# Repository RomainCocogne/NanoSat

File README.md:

### Desciption
This repo is the current work of the Smart Solar Panel Project, an auxiliary project of NiceCube.
NiceCube is a NanoSatellite project.

You can find further informations on this project following 

### Clone
If you want to clone this repo and continue the project, you need to be aware of some points

  - The code can be used as it is, but you should be carefull if you use another microcontroller. There may be some registers that need to be changed
  
  - The kicad projects use library included into this repo. If you open them as it is you might need to change the access path in kicad parameter tho.

### Contact
You can contact us using the following email adress

camille.brunin@univ-cotedazur.fr

quentin.combal@univ-cotedazur.fr

romain.cocogne@univ-cotedazur.fr

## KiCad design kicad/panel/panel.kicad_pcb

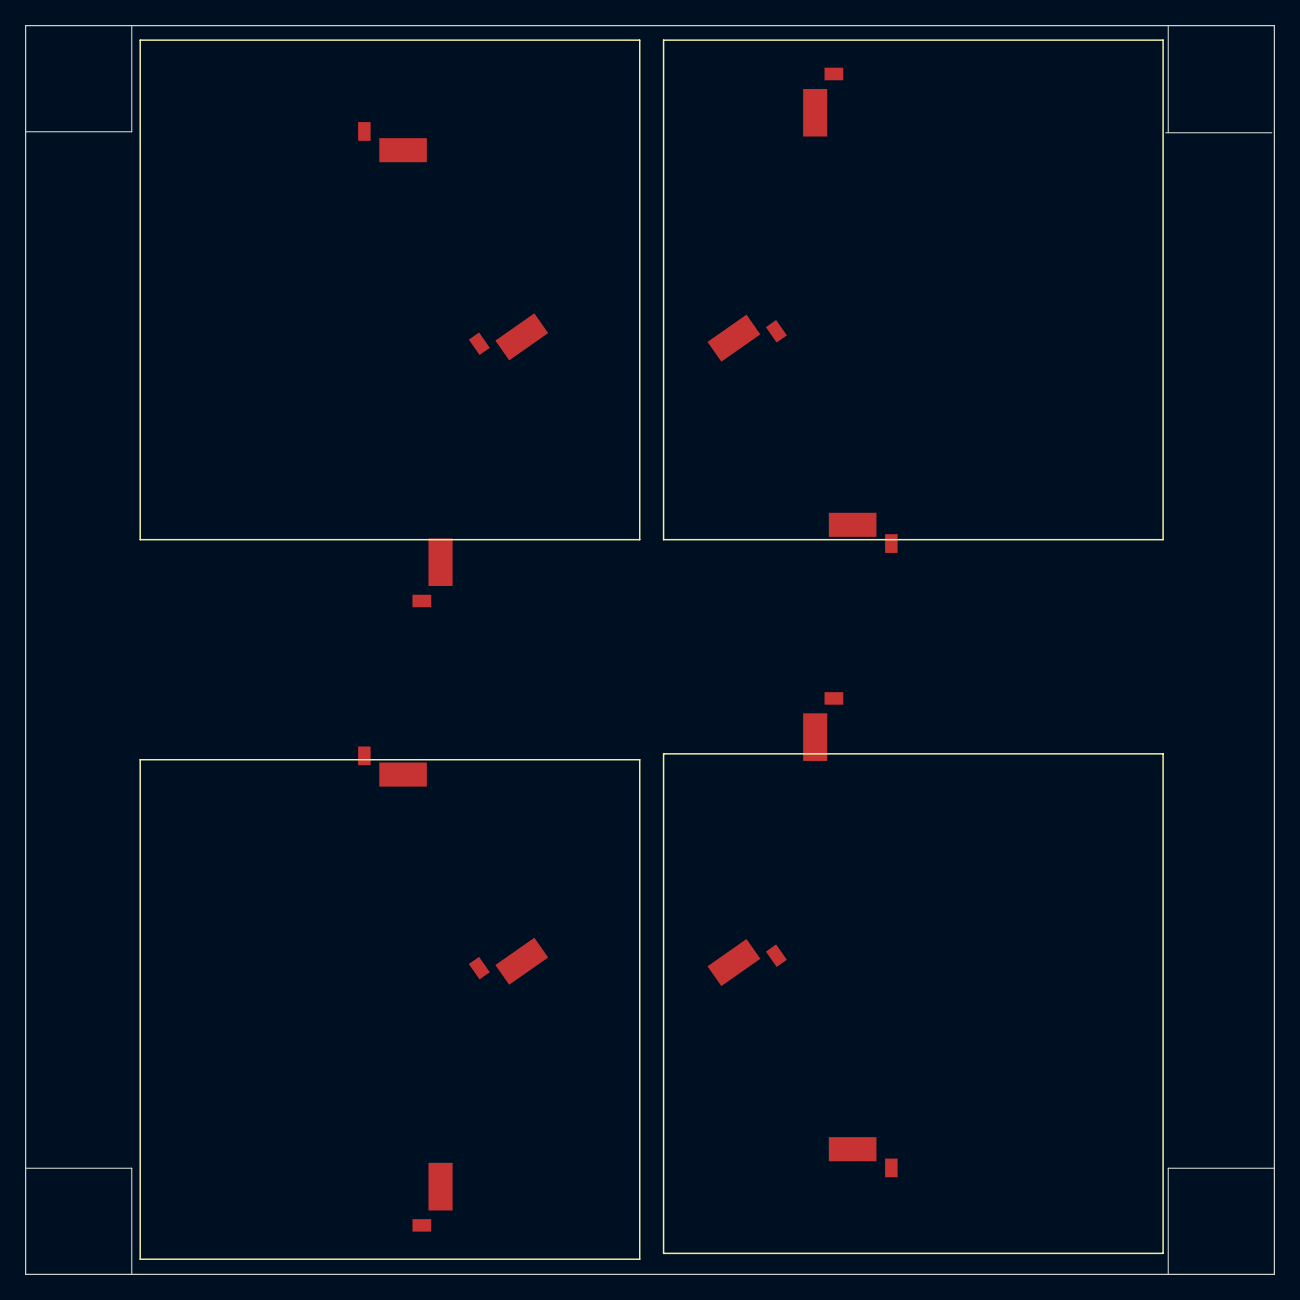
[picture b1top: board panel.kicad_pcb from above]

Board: 2 copper layers, 100.0 x 100.0 mm, 12 parts (0 on the bottom side), 11 nets, no tracks yet.

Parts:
SC1, SC2, SC3, SC4, SC5, SC6, SC7, SC8, SC9, SC10, SC11, SC12: Solar_Cell; TRISOLX-T01

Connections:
GND: SC4.2, SC8.2, SC12.2
unnamed: SC1.2, SC2.1
unnamed: SC2.2, SC3.1
unnamed: SC3.2, SC4.1
unnamed: SC5.2, SC6.1
unnamed: SC6.2, SC7.1
unnamed: SC7.2, SC8.1
unnamed: SC9.2, SC10.1
unnamed: SC10.2, SC11.1
unnamed: SC11.2, SC12.1
VCC: SC1.1, SC5.1, SC9.1

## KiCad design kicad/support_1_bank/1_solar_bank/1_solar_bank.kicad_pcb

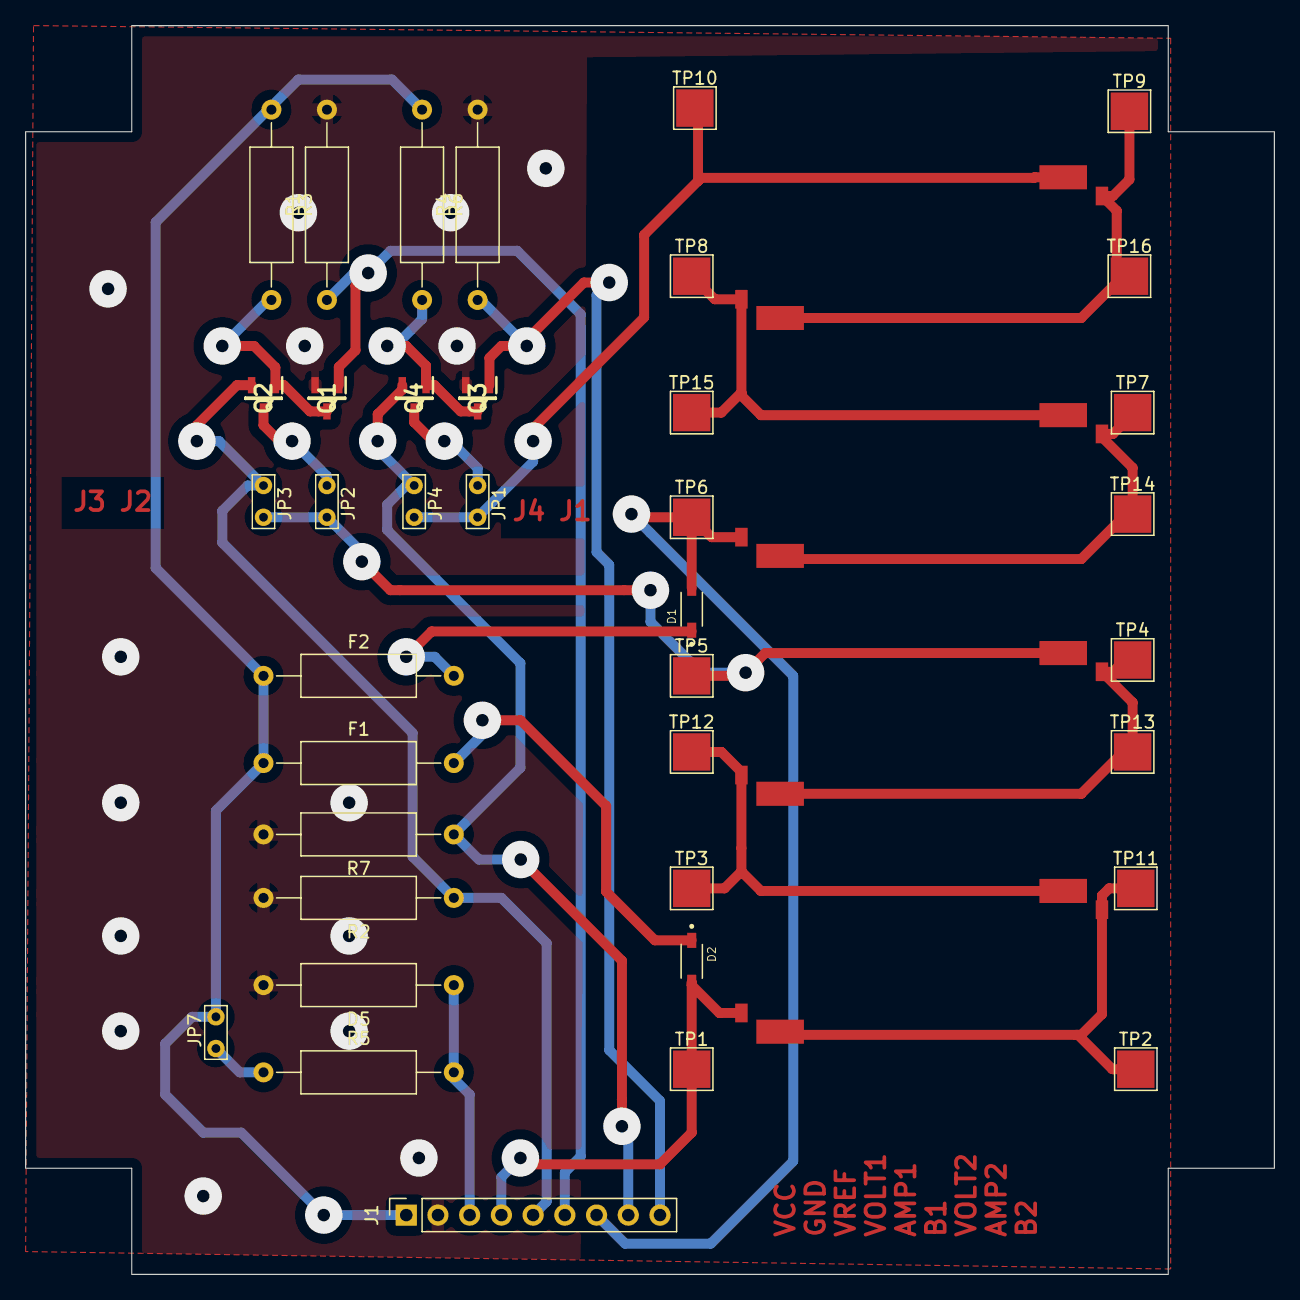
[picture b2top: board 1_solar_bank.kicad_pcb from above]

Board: 2 copper layers, 100.0 x 100.0 mm, 46 parts (0 on the bottom side), 24 nets.

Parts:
D1, D2: D_Schottky; SOD3715X135N
D5: D_Zener; R_Axial_DIN0309_L9.0mm_D3.2mm_P15.24mm_Horizontal
F1, F2: Fuse_Small; R_Axial_DIN0309_L9.0mm_D3.2mm_P15.24mm_Horizontal
J1: Conn_01x09; PinSocket_1x09_P2.54mm_Vertical
JP1, JP2, JP3, JP4, JP7: Jumper_2_Bridged; TestPoint_Bridge_Pitch2.54mm_Drill0.7mm
Q1, Q2, Q3, Q4: RUR040N02HZGTL
R1, R2, R4, R7: 20R; R_Axial_DIN0309_L9.0mm_D3.2mm_P15.24mm_Horizontal
R3, R5, R6: 1M; R_Axial_DIN0309_L9.0mm_D3.2mm_P15.24mm_Horizontal
SC1, SC2, SC3, SC4, SC5, SC6, SC7, SC8: Solar_Cell; TRISOLX-T01
TP1, TP2, TP3, TP4, TP5, TP6, TP7, TP8, TP9, TP10, TP11, TP12, TP13, TP14, TP15, TP16: TestPoint; TestPoint_Pad_3.0x3.0mm

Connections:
+VSW: F1.1, F2.1, J1.1, JP7.1, R3.1, R6.1
AMPERMETER1: J1.5, JP3.2, Q2.3, R2.1
AMPERMETER2: J1.8, JP4.2, Q4.3, R7.1
BNK1_CONTROL: J1.6, Q1.1, R1.1
BNK2_CONTROL: J1.9, Q3.1, R4.1
GND: D5.2, J1.2, Q1.3, Q3.3, R1.2, R2.2, R4.2, R7.2
unnamed: D1.1, F2.2
unnamed: D2.1, F1.2
unnamed: JP1.1, JP4.1, SC8.2, TP10.1
unnamed: JP1.2, Q4.2
unnamed: JP2.1, JP3.1, SC4.2, TP5.1
unnamed: JP2.2, Q2.2
unnamed: JP7.2, R5.1
unnamed: Q1.2, Q2.1, R3.2
unnamed: Q3.2, Q4.1, R6.2
unnamed: SC1.2, SC2.1, TP2.1, TP11.1
unnamed: SC2.2, SC3.1, TP3.1, TP12.1
unnamed: SC3.2, SC4.1, TP4.1, TP13.1
unnamed: SC5.2, SC6.1, TP7.1, TP14.1
unnamed: SC6.2, SC7.1, TP8.1, TP15.1
unnamed: SC7.2, SC8.1, TP9.1, TP16.1
VOLTMETER1: D2.2, J1.4, SC1.1, TP1.1
VOLTMETER2: D1.2, J1.7, SC5.1, TP6.1
V_REF: D5.1, J1.3, R5.2

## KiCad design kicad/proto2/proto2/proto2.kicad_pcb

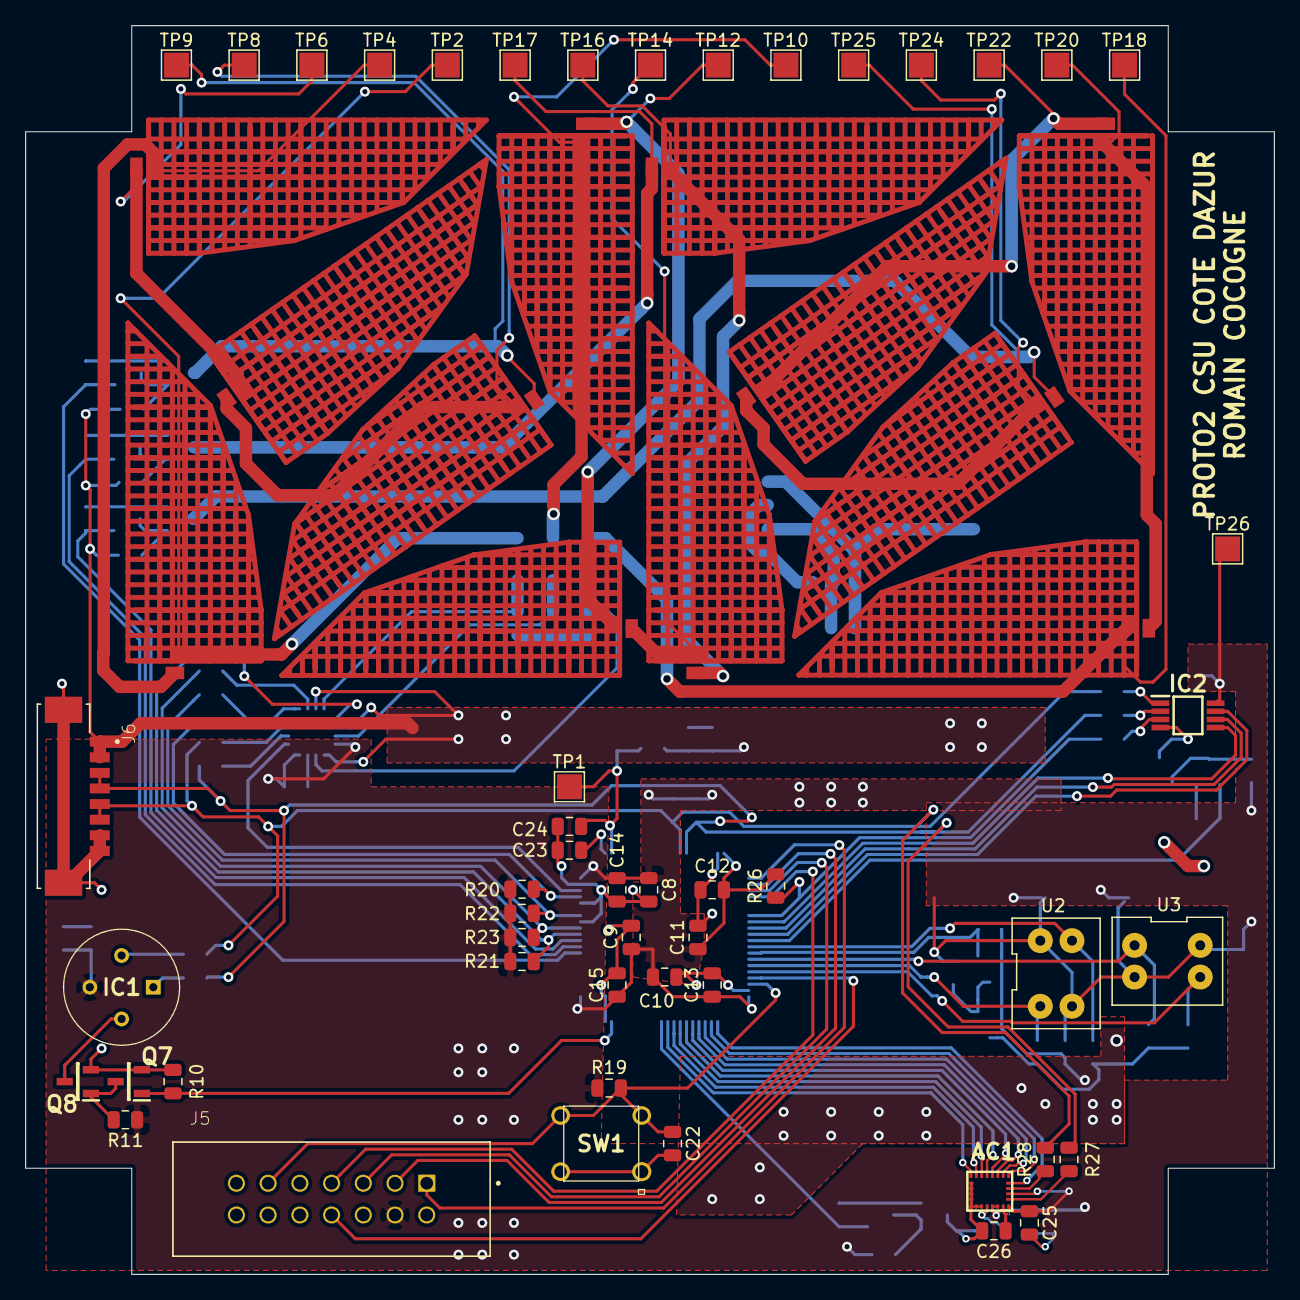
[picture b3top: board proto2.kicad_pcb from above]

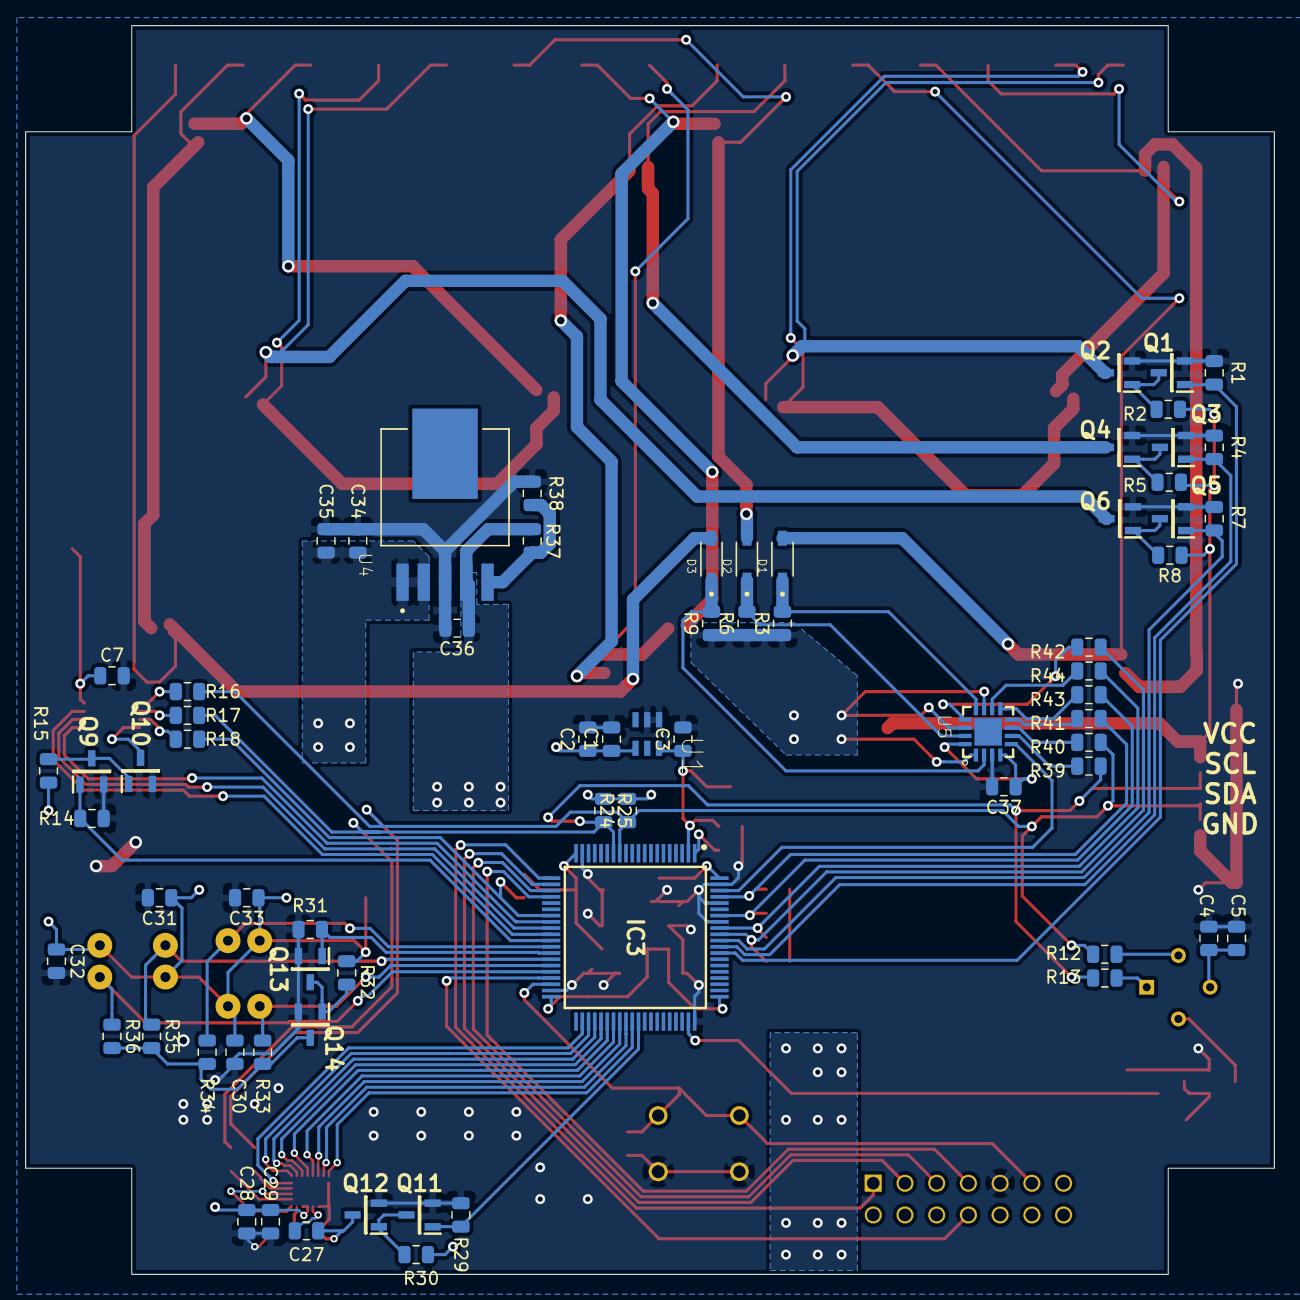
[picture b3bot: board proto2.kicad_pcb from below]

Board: 2 copper layers, 100.0 x 100.0 mm, 132 parts (70 on the bottom side), 87 nets.

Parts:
AC1: LSM9DS1TR; LGA-24L_3X3.5X1MM_
C1, C5, C7, C23, C24, C25, C26, C28, C30, C31, C32, C33, C34, C37: 100nF; C_0805_2012Metric
C2, C3: 1uF; C_0805_2012Metric
C4, C8, C9, C10, C11, C29: 10uF; C_0805_2012Metric
C12, C13, C14, C15, C27: 10nF; C_0805_2012Metric
C22: 2.2nF; C_0805_2012Metric
C35: 2.2uF; C_0805_2012Metric
C36: 47nF; C_0805_2012Metric
D1, D2, D3: D_Schottky; SOD3715X135N
IC1: MLX90641ESF-BAA-000-TU; MLX90621ESFBAB000SP
IC2: PCT2075DP,118; SOP65P490X110-8N
IC3: MSP430FR5964IPNR; QFP50P1400X1400X160-80N
J5: HEADER_2x7_2.54MM; TE_5104338-2
J6: 0532610871; MOLEX_0532610871
Q1, Q2, Q3, Q4, Q5, Q6, Q7, Q8, Q9, Q10, Q11, Q12, Q13, Q14: RUR040N02HZGTL
R1, R4, R7, R10, R14, R29, R31: 20R; R_0805_2012Metric
R2, R5, R8, R11, R15, R30, R32: 1M; R_0805_2012Metric
R3, R6, R9: 100mR; R_0805_2012Metric
R12, R13, R16, R17, R18, R27, R28, R39, R40, R41, R42, R43, R44: 330R; R_0805_2012Metric
R19: 47kR; R_0805_2012Metric
R20, R21, R22, R23, R24, R25, R26, R33, R34, R35, R36: 10k; R_0805_2012Metric
R37: 3.3k; R_0805_2012Metric
R38: 2k; R_0805_2012Metric
SC1, SC2, SC3, SC4, SC5, SC6, SC7, SC8, SC9, SC10, SC11, SC12: Solar_Cell; TRISOLX-T01
SW1: BP_DROIT_TRAV-switch; switch_fsm6jh_tyco
TP1, TP2, TP4, TP6, TP8, TP9, TP10, TP12, TP14, TP16, TP17, TP18, TP20, TP22, TP24, TP25, TP26: TestPoint; TestPoint_Pad_2.0x2.0mm
U1: LT1790ACS6-1.25TRMPBF; SOT95P280X100-6N
U2, U3: S3274-05
U4: NCP59302DSADJR4G
U5: INA3221AIRGVR; QFN65P400X400X100-17N

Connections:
/photo_diode/GND_PHOTO: Q14.2, R33.2, R34.2, R35.2, R36.2
AMPERMETER1+: D1.1, R3.2, U5.12
AMPERMETER2+: D2.1, R6.2, U5.15
AMPERMETER3+: D3.1, R9.2, U5.2
AMPERMETER-: C1.1, C2.1, C34.1, C35.1, J6.1, J6.2, R2.1, R3.1, R5.1, R6.1, R8.1, R9.1, U1.4, U4.1, U4.2, U5.1, U5.11, U5.14
AMP_A0: IC3.78, U5.5
AMP_CRITICAL: IC3.74, R22.1, R43.1
AMP_PV: IC3.72, R23.2, R44.1
AMP_TC: IC3.71, R21.2, R42.1
AMP_WARNING: IC3.77, R20.1, R41.1
BNK1_CONTROL: IC3.68, Q1.1, R1.1
BNK2_CONTROL: IC3.69, Q3.1, R4.1
BNK3_CONTROL: IC3.70, Q5.1, R7.1
CAMERA_CONTROL: IC3.59, Q7.1, R10.1
JTAG_RST: C22.1, IC3.38, J5.11, R19.2, SW1.3, SW1.4
JTAG_TCK: IC3.24, J5.7
JTAG_TDI: IC3.22, J5.3
JTAG_TDO: IC3.21, J5.1
JTAG_TEST: IC3.37, J5.8
JTAG_TMS: IC3.23, J5.5
JTAG_VCC-TARGET: AC1.1, AC1.3, AC1.22, AC1.23, C4.1, C5.1, C7.1, C8.1, C9.1, C10.1, C11.1, C12.1, C13.1, C14.1, C15.1, C25.1, C28.1, C29.1, C30.1, C31.1, C32.1, C33.1, C36.1, C37.1, IC1.3, IC2.8, IC3.20, IC3.40, IC3.61, IC3.80, J5.4, R11.1, R15.1, R19.1, R20.2, R21.1, R22.2, R23.1, R24.2, R25.1, R26.2, R30.1, R32.1, R37.1, TP26.1, U2.2, U2.4, U3.2, U3.4, U4.4, U5.4, U5.16
MAGNETOMETER_CONTROL: IC3.51, Q11.1, R29.1
MAGN_CS_AG: AC1.7, IC3.44
MAGN_CS_M: AC1.8, IC3.45
MAGN_DEN_AG: AC1.13, IC3.50
MAGN_DRDY_M: AC1.9, IC3.46
MAGN_INT1_AG: AC1.11, IC3.48
MAGN_INT2_AG: AC1.12, IC3.49
MAGN_INT_M: AC1.10, IC3.47
MAGN_SDO_AG: AC1.5, IC3.42
MAGN_SDO_M: AC1.6, IC3.43
unnamed: AC1.2, R27.1
unnamed: AC1.4, R28.1
unnamed: AC1.14, AC1.15, AC1.16, AC1.17, AC1.18, AC1.19, AC1.20, C26.2, C27.2, Q12.2
unnamed: AC1.21, C27.1
unnamed: AC1.24, C26.1
unnamed: IC1.1, R13.2
unnamed: IC1.2, R12.2
unnamed: IC1.4, Q8.2
unnamed: IC2.1, R16.1
unnamed: IC2.2, R17.1
unnamed: IC2.3, R18.1
unnamed: IC2.4, Q10.2
unnamed: Q1.2, Q2.1, R2.2
unnamed: Q2.2, SC4.2, TP9.1
unnamed: Q3.2, Q4.1, R5.2
unnamed: Q4.2, SC8.2, TP17.1
unnamed: Q5.2, Q6.1, R8.2
unnamed: Q6.2, SC12.2, TP25.1
unnamed: Q7.2, Q8.1, R11.2
unnamed: Q9.2, Q10.1, R15.2
unnamed: Q11.2, Q12.1, R30.2
unnamed: Q13.2, Q14.1, R32.2
unnamed: R37.2, R38.1, U4.5
unnamed: R39.1, U5.6
unnamed: R40.1, U5.7
unnamed: R41.2, U5.8
unnamed: R42.2, U5.13
unnamed: R43.2, U5.9
unnamed: R44.2, U5.10
unnamed: SC1.2, SC2.1, TP4.1
unnamed: SC2.2, SC3.1, TP6.1
unnamed: SC3.2, SC4.1, TP8.1
unnamed: SC5.2, SC6.1, TP12.1
unnamed: SC6.2, SC7.1, TP14.1
unnamed: SC7.2, SC8.1, TP16.1
unnamed: SC9.2, SC10.1, TP20.1
unnamed: SC10.2, SC11.1, TP22.1
unnamed: SC11.2, SC12.1, TP24.1
PHOTO1_+: IC3.35, R33.1, U2.1
PHOTO1_-: IC3.32, R34.1, U2.3
PHOTO2_+: IC3.34, R35.1, U3.1
PHOTO2_-: IC3.36, R36.1, U3.3
PHOTO_CONTROL: IC3.33, Q13.1, R31.1
SCL: IC3.14, J6.3, J6.4, R13.1, R17.2, R25.2, R27.2, R39.2
SDA: IC3.13, J6.5, J6.6, R12.1, R16.2, R24.1, R28.2, R40.2
TEMP-A0: IC2.7, IC3.30
TEMPERATURE_CONTROL: IC3.31, Q9.1, R14.1
TEMP_A1: IC2.6, IC3.29
TEMP_A2: IC2.5, IC3.28
TEMP_INT: IC3.27, R18.2, R26.1
UC1: C24.2, IC3.1
UC2: C3.1, C23.1, IC3.2, TP1.1, U1.6
UC19: C1.2, C2.2, C3.2, C4.2, C5.2, C7.2, C8.2, C9.2, C10.2, C11.2, C12.2, C13.2, C14.2, C15.2, C22.2, C23.2, C24.1, C25.2, C28.2, C29.2, C30.2, C31.2, C32.2, C33.2, C34.2, C35.2, C36.2, C37.2, IC3.19, IC3.39, IC3.60, IC3.73, IC3.76, IC3.79, J5.9, J6.7, J6.8, J6.S1, J6.S2, Q1.3, Q2.3, Q3.3, Q4.3, Q5.3, Q6.3, Q7.3, Q8.3, Q9.3, Q10.3, Q11.3, Q12.3, Q13.3, Q14.3, R1.2, R4.2, R7.2, R10.2, R14.2, R29.2, R31.2, R38.2, SW1.1, SW1.2, U1.1, U1.2, U4.3, U5.3
VOLTMETER1: D1.2, SC1.1, TP2.1
VOLTMETER2: D2.2, SC5.1, TP10.1
VOLTMETER3: D3.2, SC9.1, TP18.1

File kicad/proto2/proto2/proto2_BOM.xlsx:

Item | Qty | Reference(s) | Value | Datasheet
1 | 1 | AC1 | LSM9DS1TR | http://www.st.com/content/ccc/resource/technical/document/da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
2 | 14 | C1, C5, C7, C23, C24, C25, C26, C28, C30, C31, C32, C33, C34, C37 | 100nF | ~
3 | 2 | C2, C3 | 1uF | ~
4 | 6 | C4, C8, C9, C10, C11, C29 | 10uF | ~
5 | 5 | C12, C13, C14, C15, C27 | 10nF | ~
6 | 1 | C22 | 2.2nF | ~
7 | 1 | C35 | 2.2uF | ~
8 | 1 | C36 | 47nF | ~
9 | 3 | D1, D2, D3 | D_Schottky | ~
10 | 1 | IC1 | MLX90641ESF-BAA-000-TU | https://www.mouser.com/datasheet/2/734/MLX90614-Datasheet-Me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
11 | 1 | IC2 | PCT2075DP,118 | http://www.nxp.com/docs/en/data-sheet/PCT2075.pdf
12 | 1 | IC3 | MSP430FR5964IPNR | http://www.ti.com/general/docs/suppproductinfo.tsp?distId=10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
13 | 1 | J5 | HEADER_2x7_2.54MM
14 | 1 | J6 | 532610871 | ~
15 | 14 | Q1, Q2, Q3, Q4, Q5, Q6, Q7, Q8, Q9, Q10, Q11, Q12, Q13, Q14 | RUR040N02HZGTL | ~
16 | 7 | R1, R4, R7, R10, R14, R29, R31 | 20R | ~
17 | 7 | R2, R5, R8, R11, R15, R30, R32 | 1M | ~
18 | 3 | R3, R6, R9 | 100mR
19 | 13 | R12, R13, R16, R17, R18, R27, R28, R39, R40, R41, R42, R43, R44 | 330R
20 | 1 | R19 | 47kR
21 | 11 | R20, R21, R22, R23, R24, R25, R26, R33, R34, R35, R36 | 10k
22 | 1 | R37 | 3.3k
23 | 1 | R38 | 2k
24 | 12 | SC1, SC2, SC3, SC4, SC5, SC6, SC7, SC8, SC9, SC10, SC11, SC12 | Solar_Cell | ~
25 | 1 | SW1 | BP_DROIT_TRAV-switch
26 | 1 | U1 | LT1790ACS6-1.25TRMPBF | LT1790ACS6-1.25#TRMPBF
27 | 2 | U2, U3 | S3274-05
28 | 1 | U4 | NCP59302DSADJR4G | http://ww1.microchip.com/downloads/en/DeviceDoc/MCP14A0303_4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
29 | 1 | U5 | INA3221AIRGVR | Texas Instruments

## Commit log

2019-10-17 Add budget
2019-10-17 Gantt Projet
2019-10-17 Add memo 2
2019-10-25 update gantt: changement date visite observatoire au 22/11
2019-11-07 update gantt
    rajout de 3 tâches
2019-11-07 Memo 3
2019-11-08 update gantt: s1 & s2
2019-11-08 template mémo
2019-11-08 update gantt
2019-11-08 Ajout memo seance 3 et choix uControleur
2019-11-14 add datasheet uControleur
2019-11-14 Add datasheets
2019-11-14 datasheet panneaux solaires
2019-11-15 datasheet diode zener 1.8
2019-11-15 Memo 4 + gantt
2019-11-15 Add 2 datasheets
2019-11-15 gantt update
2019-11-15 Update BOM and GANTT
2019-11-20 solar pannels datasheets
2019-11-28 cahier des charges
2019-11-28 update specifications
2019-11-28 Schéma fonctionnel
2019-11-29 Screenshots & others
2020-02-07 add kicad
2020-02-07 mono cellule kicad schemas
2020-02-12 update panel schematic
2020-02-13 proto1 panel
2020-02-14 revision schemas + pcb
2020-02-21 Added CCS and Energia code for the MSP430 + datasheets
2020-02-21 Added I2C_ping and Magnetometer programs for the MSP430
2020-03-06 Added functional code for the LSM9DS1 magnetometer
2020-03-19 update avec le code du capteur d'horizon
2020-03-20 Ajout du calcul de l'offset pour le capteur de temperature
2020-03-27 update 27/03/2020
2020-04-08 Added CCS code for I2C connection and example code for TempSensor
2020-04-24 update on proto2
2020-05-01 Added i2c slave code
    Added CCS code for the MSP430 to act as i2c slave with a arduino as a master
2020-05-02 V2 of test_i2c_slave program
    Updated the test_i2c_slave program to read different sensors. Also updated the master_receive arduino code
2020-05-15 Added mag sensor i2c communicaton example
2020-05-21 More commands for the i2c communication
    Added more commands to the i2c_slave program for the MSP430. Updated the master_writer arduino program to test those commands.
2020-05-23 commit windows
2020-05-23 pdf et png proto2
2020-05-23 try to merge with windows
2020-05-23 BOM proto2 in exel
2020-05-23 BOM proto2
2020-05-23 proto1 schematic
2020-05-29 Ignored NiceCube datasheet
2020-05-29 gitignored updated
2020-05-29 gitignore udated
2020-06-04 last commit romain linux
2020-06-04 last commit romain windows
2020-06-04 Clean up
    Cleaned up the repository for future groups
2020-06-04 Clean up 2
2020-06-04 change proto2 kicad path so that it can be used in other PC
